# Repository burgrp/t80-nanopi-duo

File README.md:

# t80-nanopi-duo
T80 compatible carrier board for NanoPi Duo

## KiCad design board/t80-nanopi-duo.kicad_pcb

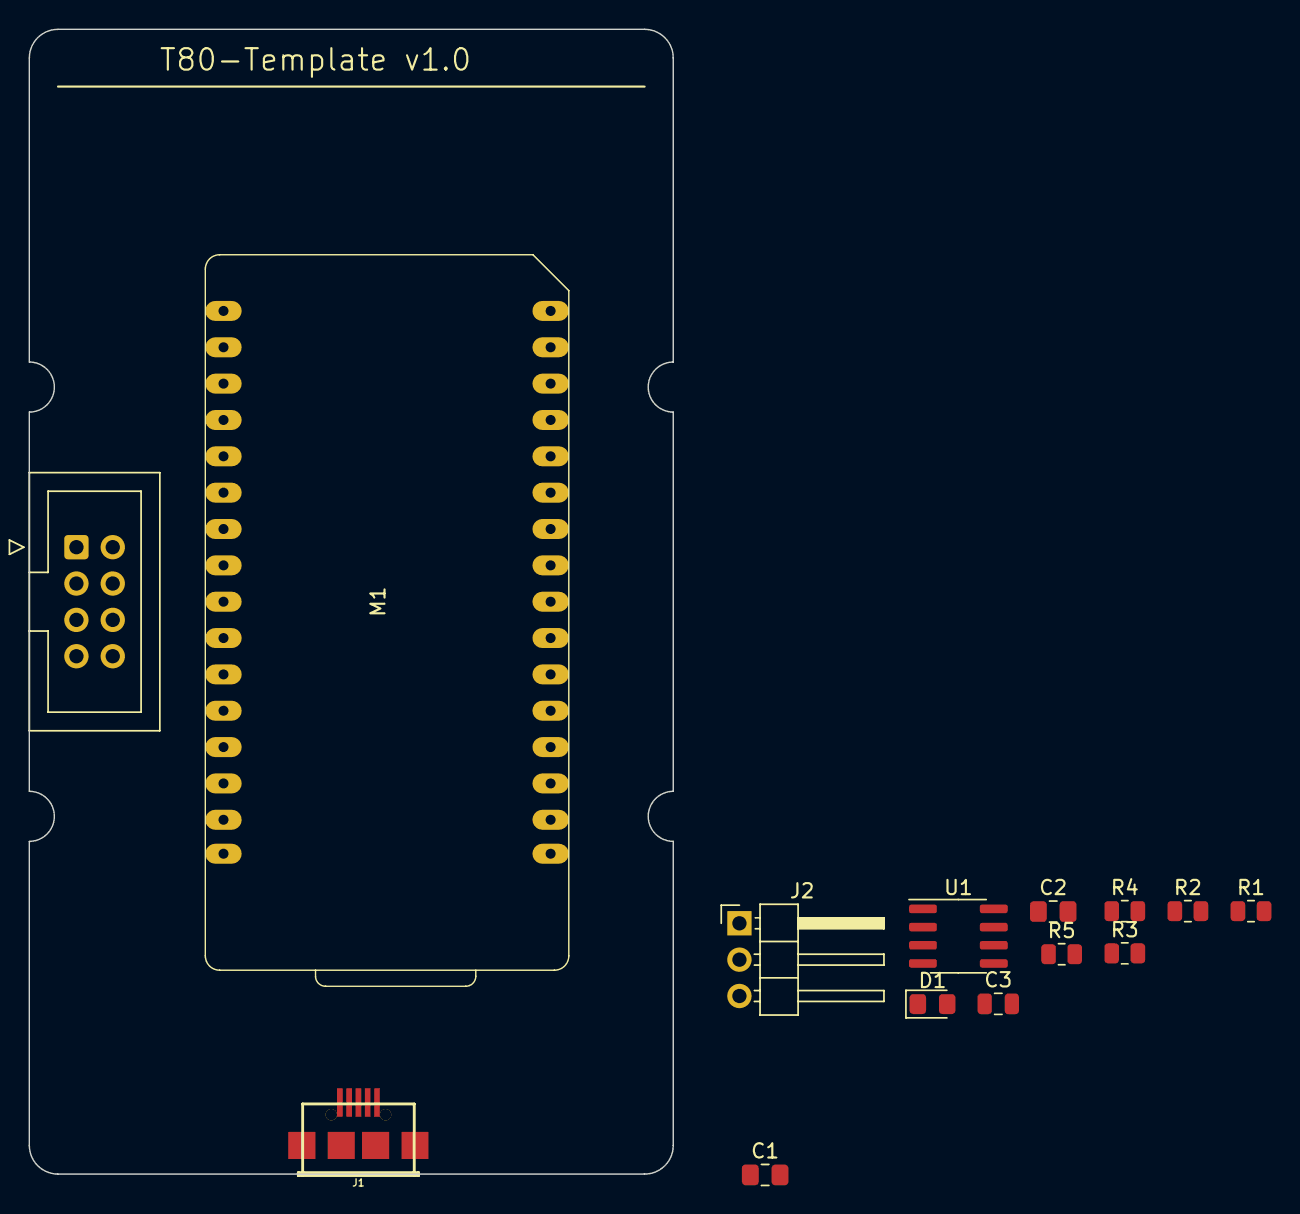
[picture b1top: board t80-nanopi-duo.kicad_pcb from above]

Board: 2 copper layers, 45.0 x 80.0 mm, 14 parts (0 on the bottom side), 14 nets, no tracks yet.

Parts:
C1, C2: 100n; C_0805_2012Metric_Pad1.18x1.45mm_HandSolder
C3: 100n; C_0805_2012Metric
D1: RED; LED_0805_2012Metric_Pad1.15x1.40mm_HandSolder
J1: USB_B_Micro; conn_usb_B_micro_smd-2
J2: UART; PinHeader_1x03_P2.54mm_Horizontal
M1: NanoPi-Duo
R1, R2, R3, R4: 1K5; R_0805_2012Metric
R5: 270R; R_0805_2012Metric
U1: CH330N; SOIC-8_3.9x4.9mm_P1.27mm
X1: IDC-Header_2x04_P2.54mm_Vertical

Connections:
+3V3: D1.2 (A), R1.2, R2.2, R3.2, R4.2, X1.4 (3V3)
+5V: M1.15 (5VIN), M1.16 (5VIN), X1.8 (5V)
/IRQ: M1.23 (UART3-RX/SPI1-CLK/IO14), R3.1, R5.1, X1.6 (IRQ)
/MY_RXD: J2.3, M1.17 (UART0-RX/PWM0/IO5), U1.6 (TXD)
/MY_TXD: J2.2, M1.18 (UART0-TX/IO4), U1.7 (RXD)
/RST: C3.2, M1.22 (UART3-TX/SPI1-CS/IO13), R4.1, X1.5 (RST)
/SCL: M1.20 (I2C0-SCL/IO11), R1.1, X1.2 (SCL)
/SDA: M1.21 (I2C0-SDA/IO12), R2.1, X1.3 (SDA)
GND: C1.2, C2.2, C3.1, J1.5 (GND), J1.6 (Shield), J2.1, M1.13 (GND), M1.19 (GND), U1.3 (GND), X1.1 (GND), X1.7 (GND)
unnamed: D1.1 (K), R5.2
unnamed: J1.3 (D+), U1.1 (UD+)
unnamed: J1.2 (D-), U1.2 (UD-)
unnamed: C1.1, J1.1 (VBUS), U1.5 (VCC)
unnamed: C2.1, U1.8 (V3)
